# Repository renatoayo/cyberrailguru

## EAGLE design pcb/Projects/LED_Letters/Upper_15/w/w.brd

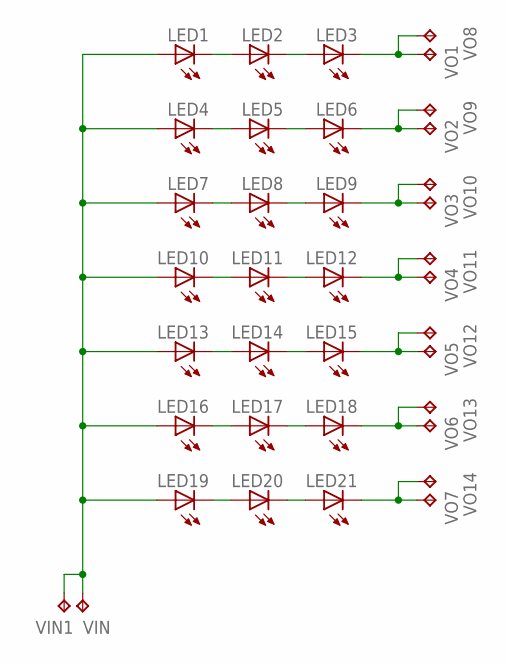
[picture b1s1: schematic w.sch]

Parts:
LED1, LED2, LED3, LED4, LED5, LED6, LED7, LED8, LED9, LED10, LED11, LED12, LED13, LED14, LED15, LED16, LED17, LED18, LED19, LED20, LED21: LED0805; LED_0805
VIN, VIN1: TEST_POINTPAD1-20; P1-20
VO1, VO2, VO3, VO4, VO5, VO6, VO7, VO8, VO9, VO10, VO11, VO12, VO13, VO14: TEST_POINTPAD1-20; P1-20

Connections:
unnamed: LED19.C, LED20.A
unnamed: LED20.C, LED21.A
unnamed: LED2.C, LED3.A
unnamed: LED1.C, LED2.A
unnamed: LED5.C, LED6.A
unnamed: LED4.C, LED5.A
unnamed: LED8.C, LED9.A
unnamed: LED7.C, LED8.A
unnamed: LED11.C, LED12.A
unnamed: LED10.C, LED11.A
unnamed: LED14.C, LED15.A
unnamed: LED13.C, LED14.A
unnamed: LED17.C, LED18.A
unnamed: LED16.C, LED17.A
VIN: LED1.A, LED4.A, LED7.A, LED10.A, LED13.A, LED16.A, LED19.A, VIN.TP, VIN1.TP
VOUT1: LED3.C, VO1.TP, VO8.TP
VOUT2: LED6.C, VO2.TP, VO9.TP
VOUT3: LED9.C, VO3.TP, VO10.TP
VOUT4: LED12.C, VO4.TP, VO11.TP
VOUT5: LED15.C, VO5.TP, VO12.TP
VOUT6: LED18.C, VO6.TP, VO13.TP
VOUT7: LED21.C, VO7.TP, VO14.TP

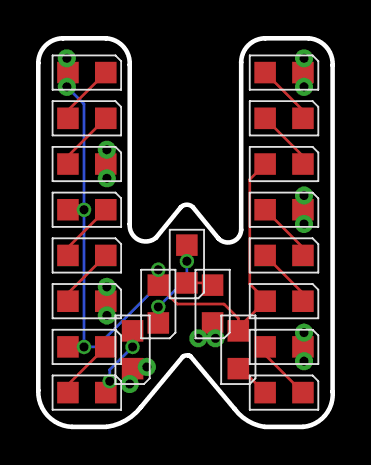
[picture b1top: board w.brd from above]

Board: 2 copper layers, 16.4 x 21.6 mm, 37 parts (0 on the bottom side), 22 nets.

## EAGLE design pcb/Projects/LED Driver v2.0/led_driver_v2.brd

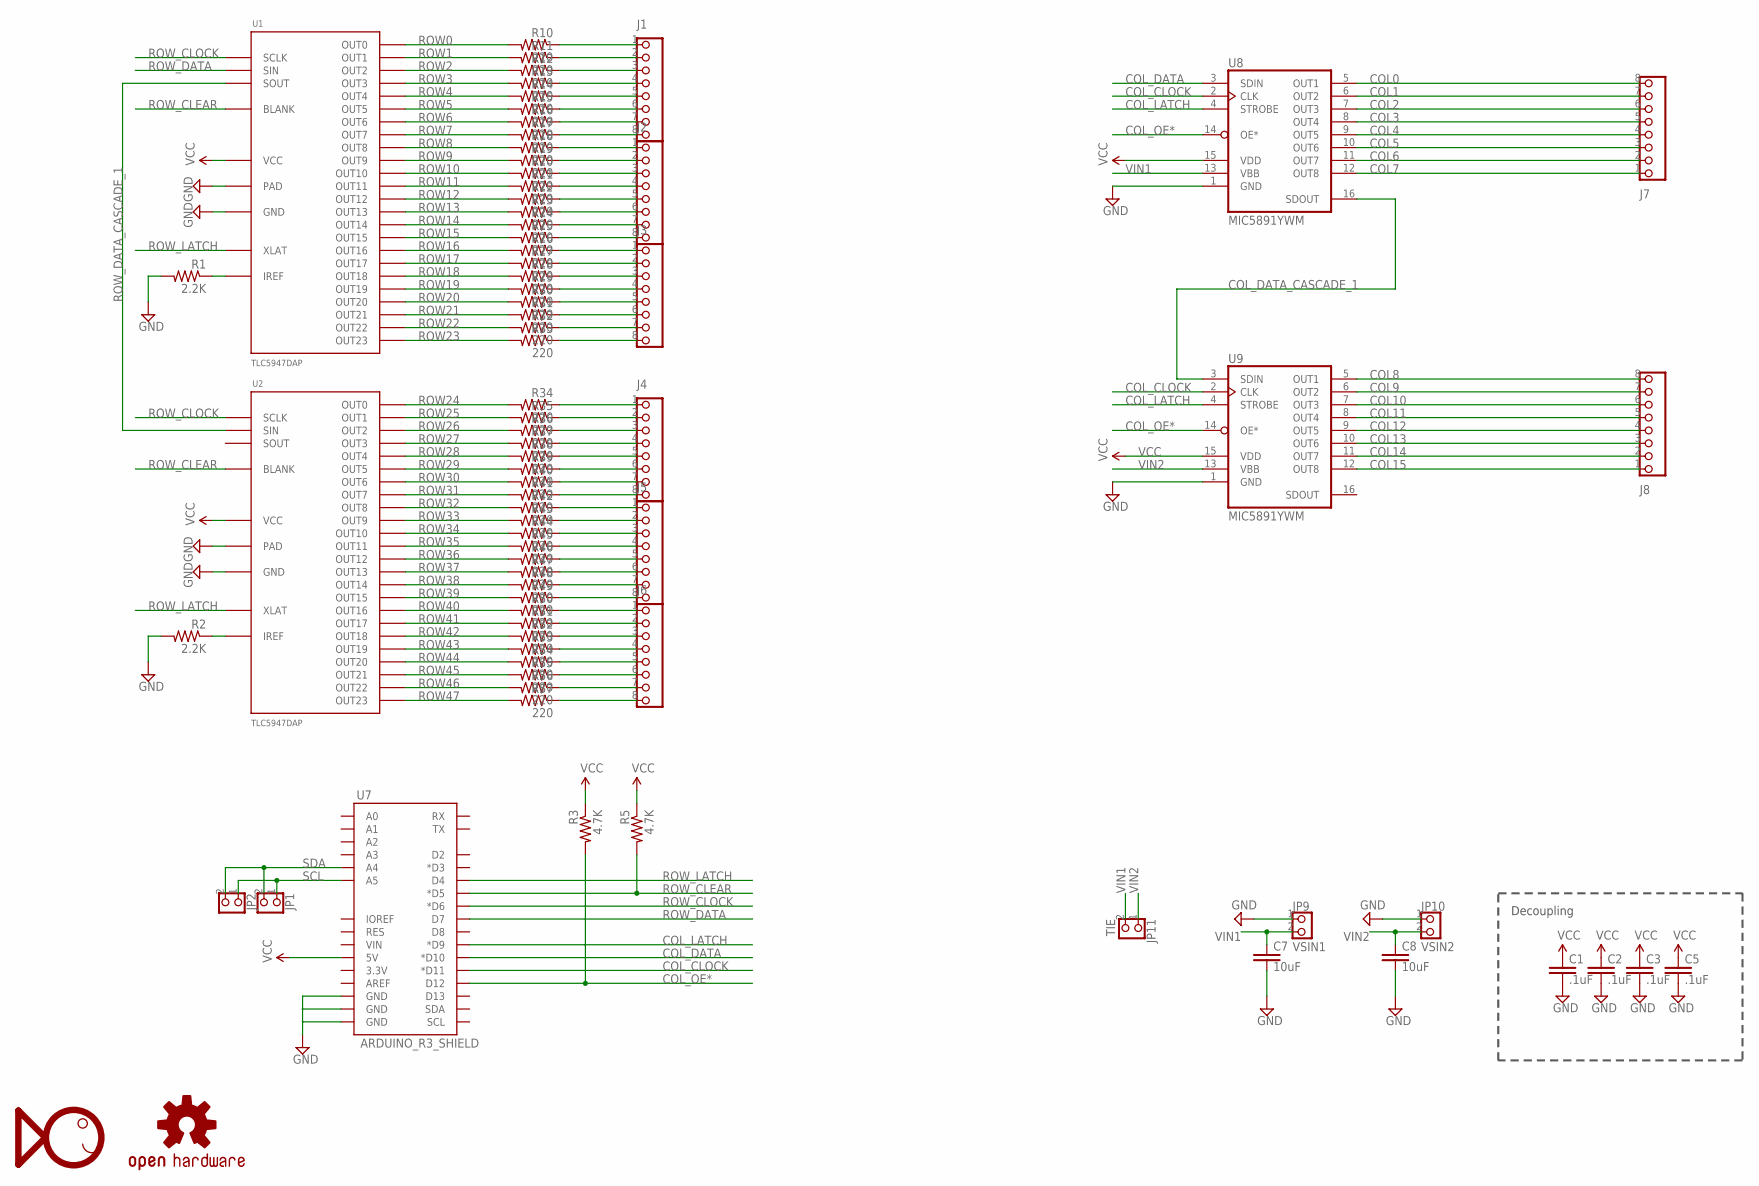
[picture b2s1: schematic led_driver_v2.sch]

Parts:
C1, C2, C3, C5: .1uF; C0603
C7, C8: 10uF; C0603
FHI_LOGO: FHI_LOGO
J1, J2, J3, J4, J5, J6, J7, J8: PINHD-1X8; 1X08
JP1, JP2: PINHD-1X2; 1X02
JP9: VSIN1; 1X02
JP10: VSIN2; 1X02
JP11: TIE; 1X02
OHW_LOGO: OSHW-LOGOS; OSHW-LOGO-S
R1, R2: 2.2K; 0603-RES
R3, R5: 4.7K; 0603-RES
R10, R11, R12, R13, R14, R15, R16, R17, R18, R19, R20, R21, R22, R23, R24, R25, R26, R27, R28, R29, R30, R31, R32, R33, R34, R35, R36, R37, R38, R39, R40, R41, R42, R43, R44, R45, R46, R47, R48, R49, R50, R51, R52, R53, R54, R55, R56, R57: 220; 0603-RES
U1, U2: TLC5947DAP; HTSSOP32DAP
U7: ARDUINO_R3_SHIELD; UNO_R3_SHIELD
U8, U9: MIC5891YWM; SO16

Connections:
COL0: J7.8, U8.5 (OUT1)
COL1: J7.7, U8.6 (OUT2)
COL2: J7.6, U8.7 (OUT3)
COL3: J7.5, U8.8 (OUT4)
COL4: J7.4, U8.9 (OUT5)
COL5: J7.3, U8.10 (OUT6)
COL6: J7.2, U8.11 (OUT7)
COL7: J7.1, U8.12 (OUT8)
COL8: J8.8, U9.5 (OUT1)
COL9: J8.7, U9.6 (OUT2)
COL10: J8.6, U9.7 (OUT3)
COL11: J8.5, U9.8 (OUT4)
COL12: J8.4, U9.9 (OUT5)
COL13: J8.3, U9.10 (OUT6)
COL14: J8.2, U9.11 (OUT7)
COL15: J8.1, U9.12 (OUT8)
COL_CLOCK: U7.D11 (*D11), U8.2 (CLK), U9.2 (CLK)
COL_DATA: U7.D10 (*D10), U8.3 (SDIN)
COL_DATA_CASCADE_1: U8.16 (SDOUT), U9.3 (SDIN)
COL_LATCH: U7.D9 (*D9), U8.4 (STROBE), U9.4 (STROBE)
COL_OE*: R3.2, U7.D12, U8.14 (OE*), U9.14 (OE*)
GND: C1.2, C2.2, C3.2, C5.2, C7.2, C8.2, JP9.1, JP10.1, R1.2, R2.2, U1.1 (GND), U1.EXP (PAD), U2.1 (GND), U2.EXP (PAD), U7.GND@0 (GND), U7.GND@1 (GND), U7.GND@2 (GND), U8.1 (GND), U9.1 (GND)
unnamed: J1.1, R10.1
unnamed: J1.7, R16.1
unnamed: J1.8, R17.1
unnamed: J2.1, R18.1
unnamed: J2.2, R19.1
unnamed: J2.3, R20.1
unnamed: J1.6, R15.1
unnamed: J2.4, R21.1
unnamed: J2.5, R22.1
unnamed: J2.6, R23.1
unnamed: R2.1, U2.31 (IREF)
unnamed: J2.7, R24.1
unnamed: J2.8, R25.1
unnamed: J3.1, R26.1
unnamed: J3.2, R27.1
unnamed: J3.3, R28.1
unnamed: J3.4, R29.1
unnamed: R1.1, U1.31 (IREF)
unnamed: J3.5, R30.1
unnamed: J3.6, R31.1
unnamed: J3.7, R32.1
unnamed: J3.8, R33.1
unnamed: J1.2, R11.1
unnamed: J1.3, R12.1
unnamed: J1.4, R13.1
unnamed: J1.5, R14.1
unnamed: J6.7, R56.1
unnamed: J6.8, R57.1
unnamed: J6.6, R55.1
unnamed: J6.5, R54.1
unnamed: J6.4, R53.1
unnamed: J6.3, R52.1
unnamed: J6.2, R51.1
unnamed: J6.1, R50.1
unnamed: J5.8, R49.1
unnamed: J5.7, R48.1
unnamed: J5.6, R47.1
unnamed: J5.5, R46.1
unnamed: J5.4, R45.1
unnamed: J5.3, R44.1
unnamed: J5.2, R43.1
unnamed: J5.1, R42.1
unnamed: J4.8, R41.1
unnamed: J4.7, R40.1
unnamed: J4.6, R39.1
unnamed: J4.5, R38.1
unnamed: J4.4, R37.1
unnamed: J4.3, R36.1
unnamed: J4.2, R35.1
unnamed: J4.1, R34.1
ROW0: R10.2, U1.5 (OUT0)
ROW1: R11.2, U1.6 (OUT1)
ROW2: R12.2, U1.7 (OUT2)
ROW3: R13.2, U1.8 (OUT3)
ROW4: R14.2, U1.9 (OUT4)
ROW5: R15.2, U1.10 (OUT5)
ROW6: R16.2, U1.11 (OUT6)
ROW7: R17.2, U1.12 (OUT7)
ROW8: R18.2, U1.13 (OUT8)
ROW9: R19.2, U1.14 (OUT9)
ROW10: R20.2, U1.15 (OUT10)
ROW11: R21.2, U1.16 (OUT11)
ROW12: R22.2, U1.17 (OUT12)
ROW13: R23.2, U1.18 (OUT13)
ROW14: R24.2, U1.19 (OUT14)
ROW15: R25.2, U1.20 (OUT15)
ROW16: R26.2, U1.21 (OUT16)
ROW17: R27.2, U1.22 (OUT17)
ROW18: R28.2, U1.23 (OUT18)
ROW19: R29.2, U1.24 (OUT19)
ROW20: R30.2, U1.25 (OUT20)
ROW21: R31.2, U1.26 (OUT21)
ROW22: R32.2, U1.27 (OUT22)
ROW23: R33.2, U1.28 (OUT23)
ROW24: R34.2, U2.5 (OUT0)
ROW25: R35.2, U2.6 (OUT1)
ROW26: R36.2, U2.7 (OUT2)
ROW27: R37.2, U2.8 (OUT3)
ROW28: R38.2, U2.9 (OUT4)
ROW29: R39.2, U2.10 (OUT5)
ROW30: R40.2, U2.11 (OUT6)
ROW31: R41.2, U2.12 (OUT7)
ROW32: R42.2, U2.13 (OUT8)
ROW33: R43.2, U2.14 (OUT9)
ROW34: R44.2, U2.15 (OUT10)
ROW35: R45.2, U2.16 (OUT11)
ROW36: R46.2, U2.17 (OUT12)
ROW37: R47.2, U2.18 (OUT13)
ROW38: R48.2, U2.19 (OUT14)
ROW39: R49.2, U2.20 (OUT15)
ROW40: R50.2, U2.21 (OUT16)
ROW41: R51.2, U2.22 (OUT17)
ROW42: R52.2, U2.23 (OUT18)
ROW43: R53.2, U2.24 (OUT19)
ROW44: R54.2, U2.25 (OUT20)
ROW45: R55.2, U2.26 (OUT21)
ROW46: R56.2, U2.27 (OUT22)
ROW47: R57.2, U2.28 (OUT23)
ROW_CLEAR: R5.2, U1.2 (BLANK), U2.2 (BLANK), U7.D5 (*D5)
ROW_CLOCK: U1.3 (SCLK), U2.3 (SCLK), U7.D6 (*D6)
ROW_DATA: U1.4 (SIN), U7.D7
ROW_DATA_CASCADE_1: U1.29 (SOUT), U2.4 (SIN)
ROW_LATCH: U1.30 (XLAT), U2.30 (XLAT), U7.D4
SCL: JP1.1, JP2.1, U7.A5
SDA: JP1.2, JP2.2, U7.A4
VCC: C1.1, C2.1, C3.1, C5.1, R3.1, R5.1, U1.32 (VCC), U2.32 (VCC), U7.5V, U8.15 (VDD), U9.15 (VDD)
VIN1: C7.1, JP9.2, JP11.2, U8.13 (VBB)
VIN2: C8.1, JP10.2, JP11.1, U9.13 (VBB)

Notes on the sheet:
Decoupling

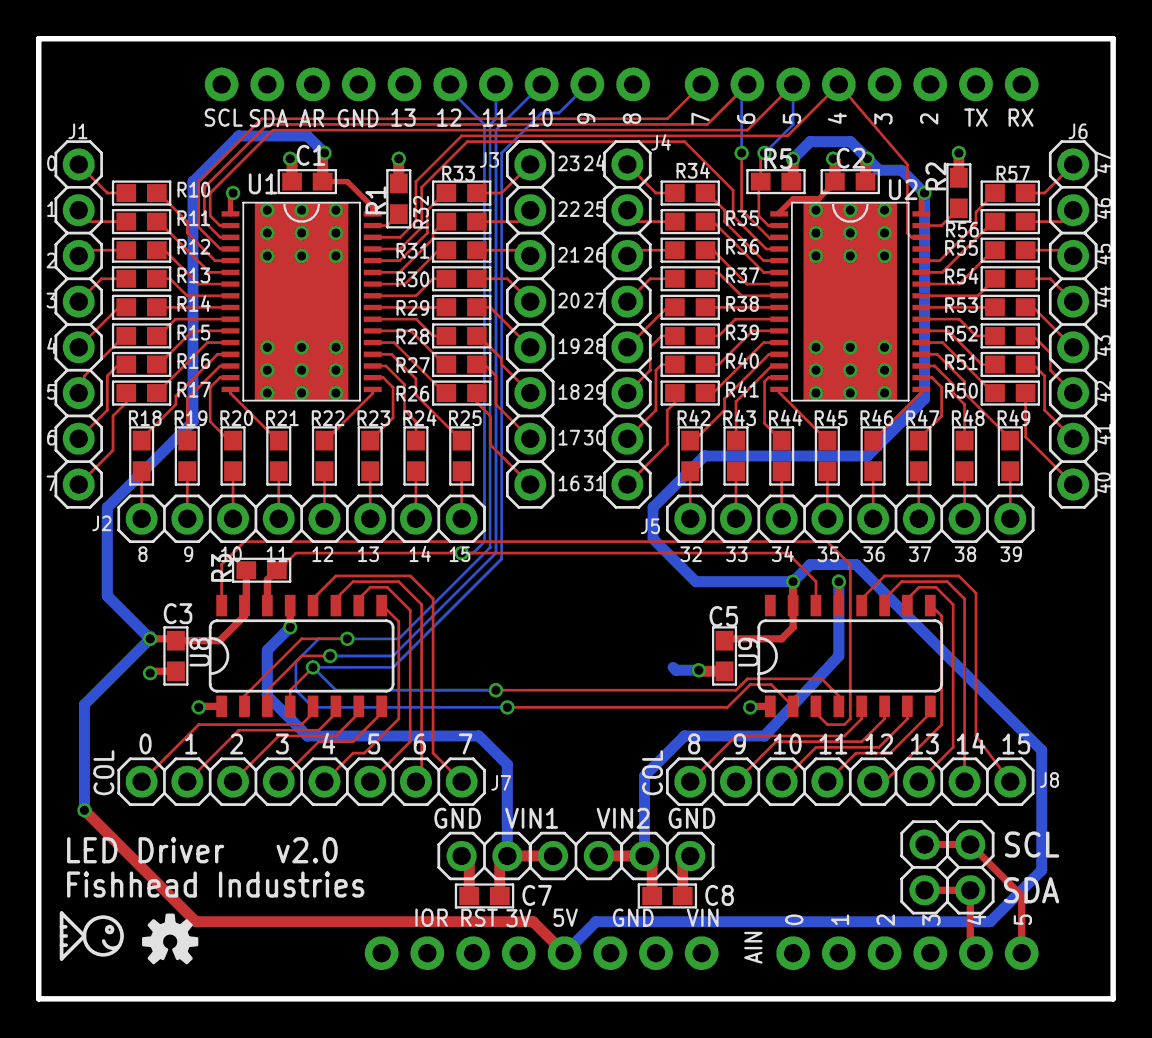
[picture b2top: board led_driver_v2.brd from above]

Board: 2 copper layers, 59.7 x 53.3 mm, 78 parts (0 on the bottom side), 130 nets.

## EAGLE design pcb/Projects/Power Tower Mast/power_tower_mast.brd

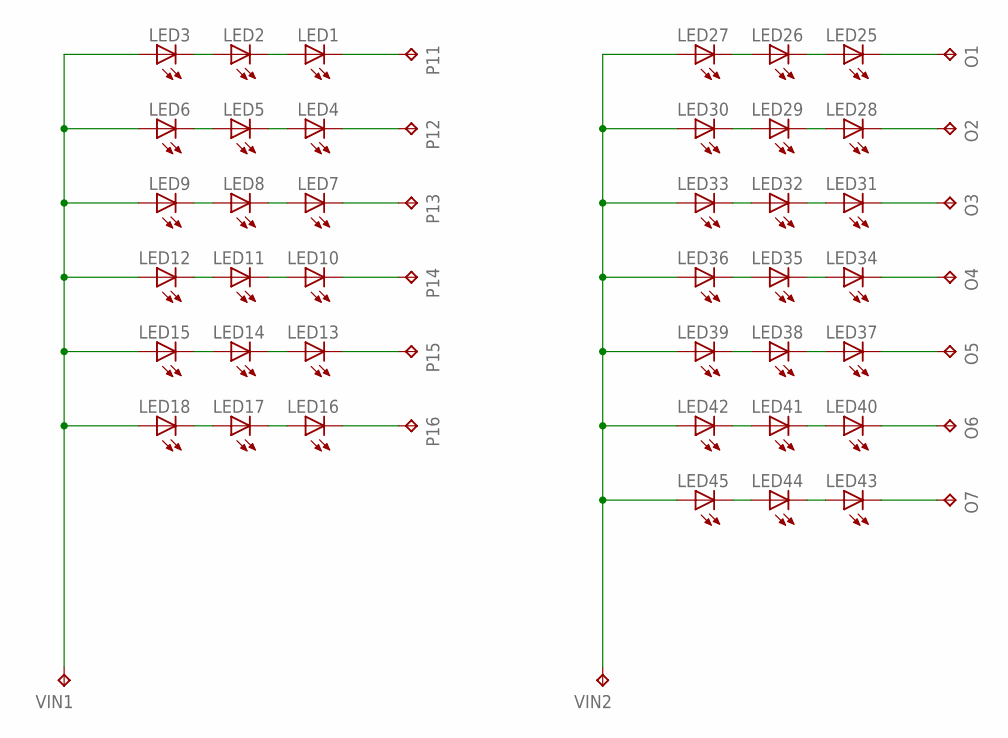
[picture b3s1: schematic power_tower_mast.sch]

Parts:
LED1, LED2, LED3, LED4, LED5, LED6, LED7, LED8, LED9, LED10, LED11, LED12, LED13, LED14, LED15, LED16, LED17, LED18, LED25, LED26, LED27, LED28, LED29, LED30, LED31, LED32, LED33, LED34, LED35, LED36, LED37, LED38, LED39, LED40, LED41, LED42, LED43, LED44, LED45: LED0805; LED_0805
O1, O2, O3, O4, O5, O6, O7: TEST_POINTPAD1-20; P1-20
P11, P12, P13, P14, P15, P16: TEST_POINTPAD1-20; P1-20
VIN1, VIN2: TEST_POINTPAD1-20; P1-20

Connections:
unnamed: LED1.A, LED2.C
unnamed: LED2.A, LED3.C
unnamed: LED25.A, LED26.C
unnamed: LED26.A, LED27.C
unnamed: LED4.A, LED5.C
unnamed: LED5.A, LED6.C
unnamed: LED28.A, LED29.C
unnamed: LED29.A, LED30.C
unnamed: LED7.A, LED8.C
unnamed: LED8.A, LED9.C
unnamed: LED31.A, LED32.C
unnamed: LED32.A, LED33.C
unnamed: LED10.A, LED11.C
unnamed: LED11.A, LED12.C
unnamed: LED34.A, LED35.C
unnamed: LED35.A, LED36.C
unnamed: LED13.A, LED14.C
unnamed: LED14.A, LED15.C
unnamed: LED37.A, LED38.C
unnamed: LED38.A, LED39.C
unnamed: LED16.A, LED17.C
unnamed: LED17.A, LED18.C
unnamed: LED40.A, LED41.C
unnamed: LED41.A, LED42.C
unnamed: LED43.A, LED44.C
unnamed: LED44.A, LED45.C
VIN: LED3.A, LED6.A, LED9.A, LED12.A, LED15.A, LED18.A, VIN1.TP
VIN1: LED27.A, LED30.A, LED33.A, LED36.A, LED39.A, LED42.A, LED45.A, VIN2.TP
VOUT1: LED1.C, P11.TP
VOUT2: LED4.C, P12.TP
VOUT3: LED7.C, P13.TP
VOUT4: LED10.C, P14.TP
VOUT5: LED13.C, P15.TP
VOUT6: LED16.C, P16.TP
VOUT9: LED25.C, O1.TP
VOUT10: LED28.C, O2.TP
VOUT11: LED31.C, O3.TP
VOUT12: LED34.C, O4.TP
VOUT13: LED37.C, O5.TP
VOUT14: LED40.C, O6.TP
VOUT15: LED43.C, O7.TP

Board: 2 copper layers, 54 parts (0 on the bottom side), 41 nets, no tracks yet.

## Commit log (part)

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2012-10-08 Initial import.
2012-11-23 Added uno library specifically.
2012-12-24 Updated to arduino 1.0
2012-12-24 Updated with recent project info.
2012-12-24 No clue.
2012-12-30 added project file
2013-01-08 changed project name
2013-01-08 changed to AvrLib10
2013-01-08 initial check in lib with 16Mhz
2013-01-08 removed - using diff plugin
2013-01-08 added new plugin prefs
2013-01-09 Updated project to have correct ENV variables.
2013-10-13 initial import
2013-10-13 Added write to EEPROM to save settings.
2013-11-20 Share project "TopSpin" into "https://cyberrailguru.googlecode.com/svn"
2013-11-20 Share project "Test5947" into "https://cyberrailguru.googlecode.com/svn"
2013-11-20 Share project "OLEDTest2" into "https://cyberrailguru.googlecode.com/svn"
2013-11-20 Share project "FlexiTimer" into "https://cyberrailguru.googlecode.com/svn"
2013-11-20 initial check in
2013-12-01 Share project "PowerTowerLights" into "https://cyberrailguru.googlecode.com/svn"
2013-12-01 Initial checkin
2013-12-02 Updated to use port manipulation.
2013-12-02 further optimization of code - mostly eliminated flicker. added sine-based fade test
2013-12-04 move initialization of high side from constructor to initialize method.
2013-12-04 Optimized high side driver with direct port calls; removed all old code.
2013-12-05 Continued refinement of routines. Added #ifdef __DEBUG
2013-12-08 Started process of creating LedShield class and pulling all shield specifics into that class. TODO: rename HighSideDriver to Sn74595Driver or Driver74595 (which means renaming Tlc5947Driver to Driver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
2013-12-10 working with malloc
2013-12-10 moved to calloc of flat arrays
2013-12-13 updated to use allocated buffers
2013-12-13 added column scanning. very broken but compiles.
2013-12-18 rolling columns appears to work as well as possible. limited flickering for full on; a lot of flickering for shaded values.
2014-01-26 full interrupt drive
2014-01-26 optimize code; still trying to get ghost turned off
2014-01-27 still ghosting
2014-01-28 Updated with new driver to consolidate hs and ls.
2014-01-29 works enough
2014-02-02 moved to macros for port expansion and greatly simplified the code.
2014-02-05 updated with additional patterns. Some dorky stuff with unsigned vs signed ints. Investigate on a later day.
2014-03-02 added ifdef for uno and leonardo
2014-03-02 Removed legacy code commented out LED flash
2014-03-02 refactored renamed driver2 to driver.
2014-03-02 added additional sequences.
2014-03-28 added scaled value output and expanded to be full 48x8
2014-03-30 worked on patterns; almost ready for movement.
2014-04-16 Share project "PowerTowerMotor" into "https://cyberrailguru.googlecode.com/svn"
2014-04-17 slight update so the sequence starts over again.
2014-04-17 working patterns
2014-04-17 updated leonardo reset time to 5s
2014-11-11 many updates since last sync
2014-11-11 removed temp files
2014-11-11 Share project "NeoPixelString" into "https://cyberrailguru.googlecode.com/svn"
2014-11-11 Share project "LedFlasher" into "https://cyberrailguru.googlecode.com/svn"
2014-11-11 Initial check in.
2014-11-21 updated led footprint
2014-11-21 updated with extra vias and panelized
2014-11-21 removed files that are not necessary
2014-11-21 added panel project and changed xln to txt
2014-11-21 removed unnecessary files
2014-11-21 removed unncessary files.
2014-11-22 reworking some letters
2014-11-23 fixed ratio for all letters; continued to update layouts
2014-12-01 final updates before fab. added new letters for future projects.
2014-12-01 new letters
2014-12-02 moved f from working to main folder
2014-12-02 deleted f from working; updated g
2014-12-02 moved from working to main.
2014-12-02 removed n; not sure how it got there.
2014-12-02 removed i, l, u from o directory
2014-12-03 continued working.
2014-12-03 added board outline and remade zip
2014-12-04 move from working directory to main directory.
2014-12-07 completed all letters
2014-12-07 moved to archive
2014-12-09 moved to archive folder
2014-12-09 moved to 3rd party folder
2014-12-09 Added stencil orders to version control
2014-12-09 removed backup files from eagle.
2014-12-28 Share project "PowerTowerMast" into "https://cyberrailguru.googlecode.com/svn"
2014-12-28 finished ordering and added animation
2014-12-29 updated comments and prepare for final "TODOs"
2014-12-29 changed to accept 16 columns. UNTESTED with 16 full columns though!
2014-12-30 attempted to get PWM working; failed...
2014-12-30 added library directory
2015-01-01 updated to allow brightness of LEDs full resolution.
2015-01-02 added letter array and continued to optimize.
2015-01-02 changed to use index for letters instead of passing around large pointers
2015-01-02 added kit-like routine for follow. fixed error in segment size.
2015-01-03 fixed wiring after mounting; changed BRIGHTNESS to INTENSITY
2015-01-04 tweaking display after mounting
2015-01-20 Optimized code; commented code; change patterns a little; added sparkle effect.
2015-02-09 moved to new directory
2015-02-09 moved power tower to new dir; deleted merged folder
2015-02-09 moved letters to subdirectory
2015-02-09 renamed letter directory
2015-05-26 fixed to use full bit depth. took out wireless comm test.
2015-05-26 updated design rules and cam.
2015-05-26 removed zip file.
2015-05-26 working on formats to create cam data
2015-08-06 Migrating wiki contents from Google Code

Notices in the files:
parts and their libraries:
SparkFun-Aesthetics: Licensing: CC v3.0 Share-Alike You are welcome to use this library for commercial purposes.
